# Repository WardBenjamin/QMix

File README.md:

# QMix
Audio mixer hardware design built in KiCad 5

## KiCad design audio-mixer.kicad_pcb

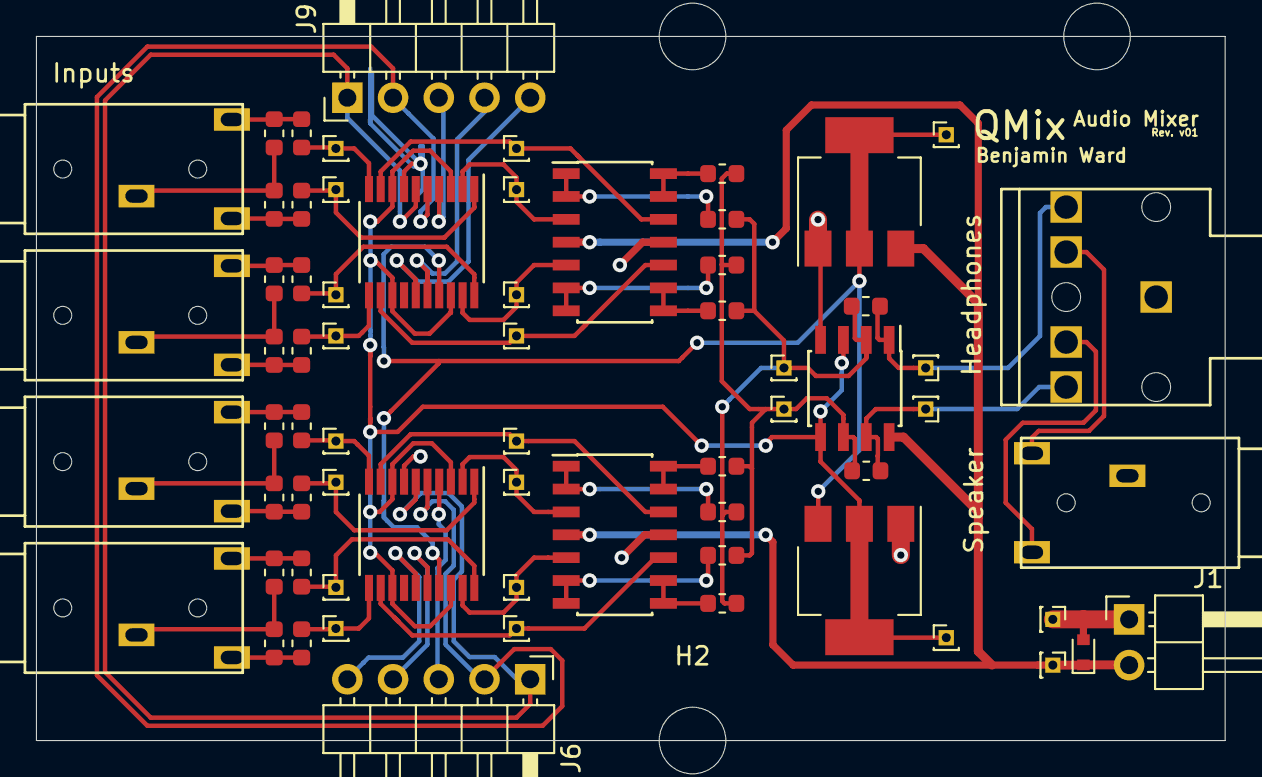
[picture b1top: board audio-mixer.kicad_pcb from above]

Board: 2 copper layers, 66.0 x 39.1 mm, 70 parts (0 on the bottom side), 50 nets.

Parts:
C1, C2, C3, C4, C5, C6, C7, C8: 1uF; C_0603_1608Metric
D1: D_TVS; D_SOD-523
H1, H2, H3: MountingHole; MountingHole_3.7mm
J1: Power Input; PinHeader_1x02_P2.54mm_Horizontal
J2: Stereo Input 1; STX-3000
J3: Stereo Input 2; STX-3000
J4: Stereo Input 3; STX-3000
J5: Stereo Input 4; STX-3000
J6, J9: Conn_01x05; PinHeader_1x05_P2.54mm_Horizontal
J7: Headphones Output; STX-3120-5B
J8: Speaker Output; STX-3000
R1, R2, R7, R8, R9, R10, R15, R16, R17, R18: 10k; C_0603_1608Metric
R3, R4, R5, R6, R11, R12, R13, R14: 10M; C_0603_1608Metric
TP1, TP2, TP3, TP4, TP5, TP6, TP7, TP8, TP9, TP10, TP11, TP12, TP13, TP14, TP15, TP16, TP17, TP18, TP19, TP20, TP21, TP22, TP23, TP24: TestPoint; PinHeader_1x01_P1.00mm_Vertical
U1: TL072; SOIC-8_3.9x4.9mm_P1.27mm
U2: LD1117S50TR_SOT223; SOT-223-3_TabPin2
U3: LD1117S25TR_SOT223; SOT-223-3_TabPin2
U4, U5: MCP4451-104; TSSOP-20_4.4x6.5mm_P0.65mm
U6, U7: TL074; SOIC-14_3.9x8.7mm_P1.27mm

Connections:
+2V5: TP24.1, U1.3, U1.5, U3.2, U4.3, U4.8, U4.13, U4.18, U5.3, U5.8, U5.13, U5.18
+5V: TP23.1, U2.2, U3.3, U4.17, U5.17
+12V: D1.1, J1.2, TP21.1, U1.8, U2.3, U6.4, U7.4
/Attenuation/A0_1: J9.3, U4.4
/Attenuation/A0_2: J6.3, U5.4
/Attenuation/A1_1: J9.4, U4.16
/Attenuation/A1_2: J6.4, U5.16
/Attenuation/LEFT_1: C1.2, J2.T, R3.1
/Attenuation/LEFT_2: C2.2, J3.T, R4.1
/Attenuation/LEFT_3: C3.2, J4.T, R5.1
/Attenuation/LEFT_4: C4.2, J5.T, R6.1
/Attenuation/LEFT_COMBINED: R1.2, R7.1, R8.1, R9.1, R10.1, TP1.1, U1.2
/Attenuation/RIGHT_1: C5.2, J2.R, R11.1
/Attenuation/RIGHT_2: C6.2, J3.R, R12.1
/Attenuation/RIGHT_3: C7.2, J4.R, R13.1
/Attenuation/RIGHT_4: C8.2, J5.R, R14.1
/Attenuation/RIGHT_COMBINED: R2.2, R15.1, R16.1, R17.1, R18.1, TP2.1, U1.6
/Attenuation/SCL: J6.2, J9.2, U4.5, U5.5
/Attenuation/SDA: J6.1, J9.1, U4.6, U5.6
/Attenuation/~RESET_1: J9.5, U4.15
/Attenuation/~RESET_2: J6.5, U5.15
/LEFT_OUT: J7.T, R1.1, TP3.1, U1.1
/RIGHT_OUT: J7.R, R2.1, TP4.1, U1.7
GND: D1.2, J1.1, J2.S, J3.S, J4.S, J5.S, J7.S, J8.S, R3.2, R4.2, R5.2, R6.2, R11.2, R12.2, R13.2, R14.2, TP22.1, U1.4, U2.1, U3.1, U4.7, U5.7, U6.11, U7.11
unnamed: C1.1, TP5.1, U4.1
unnamed: C2.1, TP6.1, U4.11
unnamed: C3.1, TP7.1, U5.1
unnamed: C4.1, TP8.1, U5.11
unnamed: C5.1, TP13.1, U4.10
unnamed: C6.1, TP14.1, U4.20
unnamed: C7.1, TP15.1, U5.10
unnamed: C8.1, TP16.1, U5.20
unnamed: J7.RN, J8.R
unnamed: J7.TN, J8.T
unnamed: R7.2, U6.1, U6.2
unnamed: R8.2, U6.8, U6.9
unnamed: R9.2, U7.1, U7.2
unnamed: R10.2, U7.8, U7.9
unnamed: R15.2, U6.13, U6.14
unnamed: R16.2, U6.6, U6.7
unnamed: R17.2, U7.13, U7.14
unnamed: R18.2, U7.6, U7.7
unnamed: TP9.1, U4.2, U6.3
unnamed: TP10.1, U4.12, U6.10
unnamed: TP11.1, U5.2, U7.3
unnamed: TP12.1, U5.12, U7.10
unnamed: TP17.1, U4.9, U6.12
unnamed: TP18.1, U4.19, U6.5
unnamed: TP19.1, U5.9, U7.12
unnamed: TP20.1, U5.19, U7.5

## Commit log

2019-08-20 Preliminary schematic for analog components
2019-08-21 Assign all footprints
2019-08-21 Add all components to layout
2019-08-21 General board organization
2019-08-22 Input layout
2019-08-24 Complete PCB layout rev. v01
